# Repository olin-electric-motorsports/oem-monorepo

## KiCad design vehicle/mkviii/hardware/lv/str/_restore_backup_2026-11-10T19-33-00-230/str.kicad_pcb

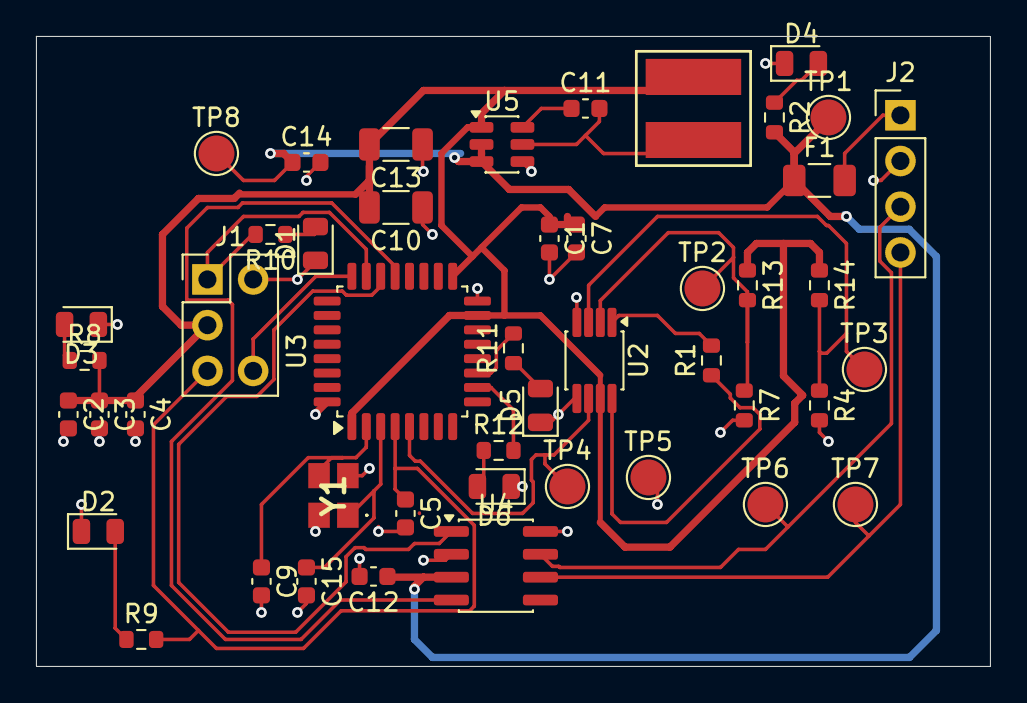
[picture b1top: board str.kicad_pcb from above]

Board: 2 copper layers, 53.0 x 35.0 mm, 47 parts (0 on the bottom side), 28 nets.

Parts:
C1: C_1uF; C_0603_1608Metric
C2, C3, C5, C11, C12: C_0.1uF; C_0603_1608Metric
C4: C_4.7uF; C_0603_1608Metric
C7: C_10uF; C_0603_1608Metric
C9, C15: C_30pF; C_0603_1608Metric
C10, C13: C_22uF; C_1206_3216Metric
C14: C_10nF; C_0603_1608Metric
D1, D2, D3, D4, D5, D6: D_Red_LED; D_0805_2012Metric
F1: F_500mA_8V; Fuse_1206_3216Metric
J1: J_Programming_Pin_Header; J_Programming_Pin_Header_Keyed
J2: Conn_01x04; PinHeader_1x04_P2.54mm_Vertical
L1: L_3.9uH; IND_BOURNS_SRR5018 (L_3.9uH_2A_55m_SMD)
R1: R_120; R_0603_1608Metric
R2, R8, R9, R10, R11, R12: R_1k; R_0603_1608Metric
R4: R_Variable; R_0603_1608Metric
R7, R13, R14: R_330; R_0603_1608Metric
TP1, TP2, TP3, TP4, TP5, TP6, TP7, TP8: TestPoint; TestPoint_Pad_D2.0mm
U2: INA333xxDGK; VSSOP-8_3x3mm_P0.65mm
U3: STM32G441KBT6; LQFP-32_7x7mm_P0.8mm
U4: MCP2561-E_SN; SOIC-8_3.9x4.9mm_P1.27mm
U5: AP63203WU-7; SOT-23-6
Y1: X_16MHz_18pF; FA238160000MBC0 (X_16MHz_18pF_SMD - FA-238_16.0000MB-C0)

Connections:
+3V3: C1.1, C2.1, C3.1, C4.1, C7.1, C10.2, C13.2, J1.3, L1.2, R8.2, R13.1, R14.1, U2.7 (V+), U3.1 (VDD), U3.15 (VDDA), U3.17 (VDD), U5.1 (FB)
+5V: C12.1, C14.1, F1.1, R2.2, TP1.1 (1_1), TP8.1 (1_1), U4.3 (VDD), U5.2 (EN), U5.3 (VIN)
/CAN_+: J2.3, TP6.1 (1_1), U4.7 (CANH)
/CAN_-: J2.4, TP7.1 (1_1), U4.6 (CANL)
/CAN_RX: U3.21 ((FDCAN1_RX/GPIO_EXTI11)PA11), U4.4 (RXD)
/CAN_TX: U3.22 ((FDCAN1_TX/GPIO_EXTI12)PA12), U4.1 (TXD)
/Debug LED: R12.2, U3.10 ((TIM2_ETR/TIM2_CH1/GPIO_EXTI5/ADC2_IN13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)
/Heartbeat LED: R11.2, U3.11 ((TIM3_CH1/TIM16_CH1/GPIO_EXTI6/ADC2_IN3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)
/NRST: C5.1, J1.4, R9.2, U3.4 ((GPIO_EXTI10)PG10-NRST)
/SWCLK: J1.5, U3.24 ((SYS_JTCK-SWCLK/GPIO_EXTI14)PA14)
/SWDIO: J1.1, R10.2, U3.23 ((SYS_JTMS-SWDIO/GPIO_EXTI13)PA13)
GND: C1.2, C2.2, C3.2, C4.2, C5.2, C7.2, C9.2, C10.1, C12.2, C13.1, C14.2, C15.2, D1.1 (K), D2.1 (K), D3.1 (K), D4.1 (K), D5.1 (K), D6.1 (K), J1.2, J2.2, R4.2, R7.2, TP5.1 (1_1), U2.4 (V-), U2.5 (Ref), U3.14 (VSSA), U3.16 (VSS), U3.32 (VSS), U4.2 (VSS), U4.8 (STBY), U5.4 (GND), Y1.2, Y1.4
unnamed: D1.2 (A), R10.1
unnamed: D2.2 (A), R9.1
unnamed: D3.2 (A), R8.1
unnamed: D4.2 (A), R2.1
unnamed: D5.2 (A), R11.1
unnamed: D6.2 (A), R12.1
unnamed: F1.2, J2.1
unnamed: R1.1, U2.8 (Rg)
unnamed: R1.2, U2.1 (Rg)
unnamed: R4.1, R14.2, TP3.1 (1_1), U2.3 (+)
unnamed: R7.1, R13.2, TP2.1 (1_1), U2.2 (-)
unnamed: TP4.1 (1_1), U2.6, U3.5 ((TIM2_ETR/TIM2_CH1/GPIO_EXTI0/ADC2_IN1/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)
unnamed: C9.1, U3.2 (PF0-OSC_IN), Y1.3
unnamed: C15.1, U3.3 (PF1-OSC_OUT), Y1.1
unnamed: C11.1, U5.6 (BST)
unnamed: C11.2, L1.1, U5.5 (SW)

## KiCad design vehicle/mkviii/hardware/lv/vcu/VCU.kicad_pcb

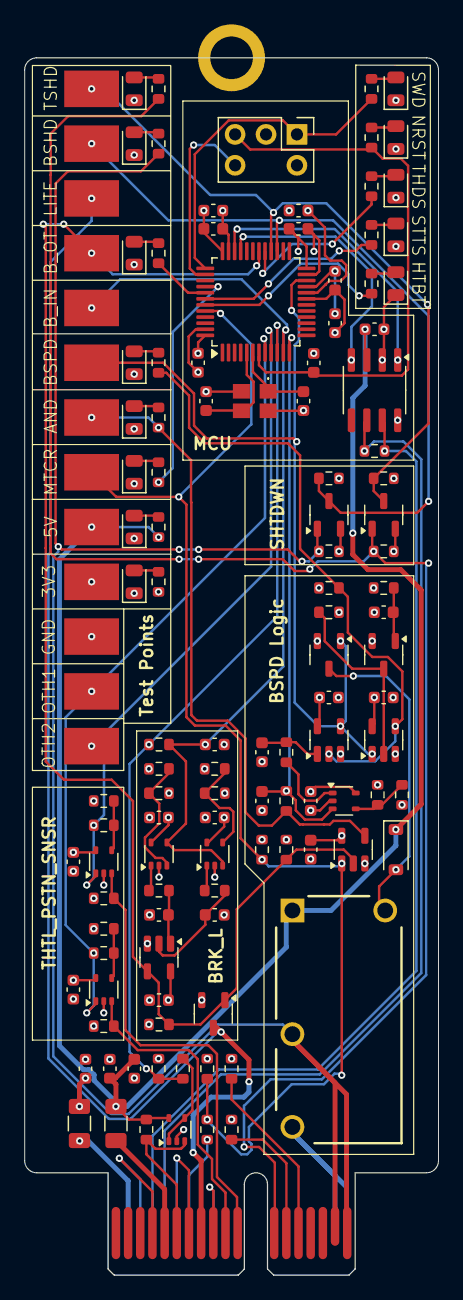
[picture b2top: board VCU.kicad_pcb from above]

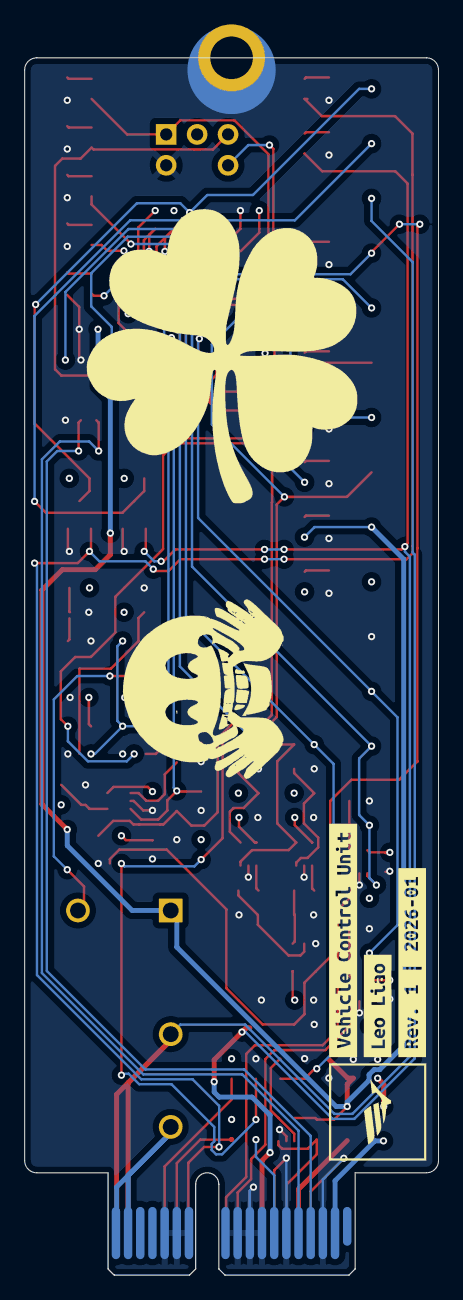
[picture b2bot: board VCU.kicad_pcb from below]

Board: 4 copper layers, 34.0 x 100.0 mm, 131 parts (3 on the bottom side), 69 nets.

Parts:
C1, C3, C5, C7, C9, C14, C15, C17, C19, C20, C21, C23, C24, C27, C28, C29: C_0.1uF; C_0603_1608Metric
C2: C_10nF; C_0603_1608Metric
C4, C18: C_1uF; C_0603_1608Metric
C6: C_4.7uF; C_0603_1608Metric
C8, C10: C_30pF; C_0603_1608Metric
C11, C26: C_0.1uF_16V; C_0603_1608Metric
C12, C13, C16: C_10uF_10V; C_0603_1608Metric
C22: C_0.22uF_50V; C_0603_1608Metric
C25: C_1uF_25V; C_0603_1608Metric
D1: MOTOR_ON; D_0805_2012Metric
D2: BRAKES; D_0805_2012Metric
D3: BSPD_TRIP; D_0805_2012Metric
D4: HEARTBEAT; D_0805_2012Metric
D5: THROTTLE_DISABLE; D_0805_2012Metric
D6: 5V; D_0805_2012Metric
D7: 3V3; D_0805_2012Metric
D8: NRST; D_0805_2012Metric
D9: SWDIO; D_0805_2012Metric
D10: D_Amber_LED; D_0805_2012Metric
D11: D_36V_500mW; D_SOD-123
D12: BSPD_TRIP_LED; D_0805_2012Metric
D13, D14: D_Blue_LED; D_0805_2012Metric
F1, F2: F_500mA_8V; Fuse_1206_3216Metric
H1: H_MountingHole
J1: J_Programming_Pin_Header; J_Programming_Pin_Header_Keyed
J2: J_PCIe_x1; J_PCIe_x1_Key
K1: K_10A_5V; G5Q1A4DC5 (K_SPST-NO_10A_5V_TH - G5Q-1A4-DC5)
Q1, Q2, Q3, Q4, Q5: SSM3K333R,LF; SOT-23-3
R1, R2, R3, R4, R5, R7, R8, R9, R12: R_200; R_0603_1608Metric
R6, R20, R27, R33: R_1k; R_0603_1608Metric
R10: R_120; R_0603_1608Metric
R11, R13, R15, R17, R22, R23, R24, R26, R28, R32, R34, R35, R36, R39, R42: R_10k; R_0603_1608Metric
R14, R16: R_5.1k; R_0603_1608Metric
R18, R19, R25, R38, R41: R_100k; R_0603_1608Metric
R21: R_71.5k; R_0603_1608Metric
R29: R_75k; R_0603_1608Metric
R30: R_576; R_0603_1608Metric
R31: R_100; R_0603_1608Metric
R37, R40: R_3k; R_0603_1608Metric
R43, R46: R_1M; R_0603_1608Metric
R44, R47: R_0; R_0603_1608Metric
R45, R48: R_2.2k; R_0603_1608Metric
TP1: 5V; TP_Hook_SMD
TP2: 3V3; TP_Hook_SMD
TP3: GND; TP_Hook_SMD
TP4, TP5, TP6, TP7, TP8, TP9, TP10, TP11, TP12, TP13: TP_SMD; TP_Hook_SMD
U1: STM32G441CBT6; LQFP-48_7x7mm_P0.5mm
U2: MCP2561-E_SN; SOIC-8_3.9x4.9mm_P1.27mm
U3, U5, U8, U9, U11, U12: MCP6001T-I/LT; SOT-353_SC-70-5
U4: SN74LVC1G08DBVR; SOT-23-5
U6, U7: SN74LVC1G02DBVR; SOT-23-5
U10: SN74LVC1G32DBVR; SOT-23-5
Y1: X_16MHz_18pF; FA238160000MBC0 (X_16MHz_18pF_SMD - FA-238_16.0000MB-C0)
kibuzzard-6983BE89: G***; kibuzzard-6983BE89
kibuzzard-6983C564: G***; kibuzzard-6983C564
kibuzzard-6983C636: G***; kibuzzard-6983C636

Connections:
+3V3: C1.1, C2.1, C3.1, C4.1, C5.1, C6.1, C7.1, C13.1, C15.2, C17.1, C20.1, C21.1, C23.1, C24.1, C27.1, C28.1, C29.1, F2.1, J1.3, R7.1, R11.1, R12.1, R18.1, R22.1, R25.1, R26.1, R30.1, R32.1, R39.1, R42.1, R43.1, R46.1, TP2.1, U1.20 (VREF+), U1.21 (VDDA), U1.24 (VDD), U1.36 (VDD), U1.48 (VDD), U4.5 (VCC), U5.5 (V+), U6.5 (VCC), U7.5 (VCC), U8.5 (V+), U9.5 (V+), U10.5 (VCC), U11.5 (V+), U12.5 (V+)
+5V: C11.1, C12.1, C14.1, D11.1 (K), F1.1, K1.1, R6.1, R13.1, TP1.1, U2.3 (VDD), U3.5 (V+)
/BSPD/BRAKELIGHT_LL: Q3.1 (G), R19.1, R36.1, TP8.1, U1.30 ((EVENTOUT/SAI1_SCK_A/SAI1_CK2/TIM4_ETR/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), U4.2, U10.4
/BSPD/BSPD_LL: Q2.1 (G), TP6.1, U1.22 ((EVENTOUT/SAI1_SCK_A/TIM1_BKIN/LPUART1_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), U6.4, U7.1
/BSPD/BSPD_RELAY_IN: J2.A17 (SHDN_IN/io_22), J2.A18 (SHDN_IN/io_24), K1.3
/BSPD/BSPD_RELAY_OUT: J2.B17 (SHDN_OUT/io_23), J2.B18 (SHDN_OUT/io_25), K1.2, Q4.1 (G), R37.1, R38.1
/BSPD/MOTOR_CURRENT_SENSE: R14.2, R15.1, R18.2, TP4.1, U1.44 ((EVENTOUT/LPTIM1_IN2/TIM3_CH4/COMP3_OUT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), U4.1
/BSPD/RC_TIMER_STATUS: C16.1, R21.2, U1.12 ((EVENTOUT/SAI1_FS_B/USART2_CK/SPI3_NSS/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), U5.3 (+)
/BrakeLight/BRAKELIGHT_CONN: J2.B8 (io_5), Q3.3 (D), TP9.1
/BrakeLight/BRAKE_PRESS_SENSE: R16.2, R17.1, R29.1, U1.10 ((EVENTOUT/UCPD1_FRSTX2/UCPD1_FRSTX1/LPU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)
/BrakeLight/BRAKE_PRESS_SENSE_FILTERED: C22.1, R29.2, TP7.1, U1.11 ((EVENTOUT/SAI1_MCLK_A/LPUART1_RX/TIM15_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), U8.4 (-), U9.3 (+)
/Microcontroller - STM32G441CBT6 (page 2)/5KW_LED: R1.1, U1.40 ((EVENTOUT/SAI1_SCK_B/TIM3_ETR/USART2_TX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)
/Microcontroller - STM32G441CBT6 (page 2)/BRAKE_LL_LED: R2.1, U1.41 ((EVENTOUT/SAI1_MCLK_B/TIM17_BKIN/USART2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)
/Microcontroller - STM32G441CBT6 (page 2)/BSPD_SHUTDOWN_SENSE: Q4.3 (D), R39.2, TP10.1, U1.27 ((EVENTOUT/LPUART1_CTS/USART3_NSS/USART3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)
/Microcontroller - STM32G441CBT6 (page 2)/BSPD_TRIP_LED: R3.1, U1.42 ((EVENTOUT/SAI1_SD_B/LPTIM1_IN1/TIM17_CH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)
/Microcontroller - STM32G441CBT6 (page 2)/CAN_+: J2.A4 (CAN+), R10.1, U2.7 (CANH)
/Microcontroller - STM32G441CBT6 (page 2)/CAN_-: J2.A5 (CAN-), R10.2, U2.6 (CANL)
/Microcontroller - STM32G441CBT6 (page 2)/CAN_RX: U1.33 ((EVENTOUT/TIM1_BKIN2/TIM1_CH4/TIM4_CH1/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), U2.4 (RXD)
/Microcontroller - STM32G441CBT6 (page 2)/CAN_TX: U1.34 ((EVENTOUT/TIM1_ETR/TIM4_CH2/FDCAN1_TX/C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), U2.1 (TXD)
/Microcontroller - STM32G441CBT6 (page 2)/HEARTBEAT_LED: R4.1, U1.43 ((EVENTOUT/SAI1_FS_B/LPTIM1_ETR/TIM8_BKI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)
/Microcontroller - STM32G441CBT6 (page 2)/NRST: C9.1, J1.4, R8.1, U1.7 ((EVENTOUT/RCC_MCO/GPIO_EXTI10)PG10-NRST)
/Microcontroller - STM32G441CBT6 (page 2)/OUTPUT_THROTTLE_1: R44.1, TP12.1, U1.8 ((EVENTOUT/TIM2_ETR/TIM8_ETR/TIM8_BKIN/C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), U11.1
/Microcontroller - STM32G441CBT6 (page 2)/OUTPUT_THROTTLE_2: R47.1, TP13.1, U1.9 ((EVENTOUT/TIM15_CH1N/USART2_DE/USART2_R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), U12.1
/Microcontroller - STM32G441CBT6 (page 2)/SS_INERTIA_OUTPUT: Q5.3 (D), R42.2, TP11.1, U1.28 ((EVENTOUT/COMP4_OUT/USART3_RTS/USART3_D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)
/Microcontroller - STM32G441CBT6 (page 2)/SWCLK: J1.5, U1.38 ((EVENTOUT/SAI1_FS_B/USART2_TX/TIM1_BKIN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)
/Microcontroller - STM32G441CBT6 (page 2)/SWDIO: J1.1, R9.1, U1.37 ((EVENTOUT/SAI1_SD_B/TIM4_CH3/USART3_NSS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)
/Microcontroller - STM32G441CBT6 (page 2)/THROTTLE_DISABLE: R5.1, U1.29 ((EVENTOUT/SPI2_MOSI/I2S2_SD/TIM1_CH3N/C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)
/PCIe x1 Connector/INPUT_THROTTLE_1: J2.B10 (io_9), R43.2, U11.3 (+)
/PCIe x1 Connector/INPUT_THROTTLE_2: J2.B11 (io_11), R46.2, U12.3 (+)
/PCIe x1 Connector/SS_INERTIA_SWITCH: J2.B12 (io_13), Q5.1 (G), R40.1, R41.1
/PCIe x1 Connector/THROTTLE_1+: J2.B13 (io_15), R11.2
/PCIe x1 Connector/THROTTLE_2+: J2.B14 (io_17), R12.2
GND: C1.2, C2.2, C3.2, C4.2, C5.2, C6.2, C7.2, C8.2, C9.2, C10.2, C11.2, C12.2, C13.2, C14.2, C15.1, C16.2, C17.2, C18.2, C19.1, C20.2, C21.2, C22.2, C23.2, C24.2, C25.2, C26.2, C27.2, C28.2, C29.2, D1.1 (K), D2.1 (K), D3.1 (K), D4.1 (K), D5.1 (K), D6.1 (K), D7.1 (K), D8.1 (K), D9.1 (K), D10.1 (K), D12.1 (K), D13.1 (K), D14.1 (K), H1.1, J1.2, J2.A3 (GND), J2.A6 (io_0), J2.A8 (io_4), J2.A9 (io_6), J2.A10 (io_8), J2.A11 (io_10), J2.A12 (io_12), J2.A13 (io_14), J2.A14 (io_16), J2.B4 (GND), J2.B7 (io_3), J2.B9 (io_7), Q1.2 (S), Q2.2 (S), Q3.2 (S), Q4.2 (S), Q5.2 (S), R15.2, R17.2, R19.2, R23.2, R28.1, R31.2, R33.2, R36.2, R38.2, R41.2, R45.2, R48.2, TP3.1, U1.19 (VSSA), U1.23 (VSS), U1.35 (VSS), U1.47 (VSS), U2.2 (VSS), U2.8 (STBY), U3.2 (V-), U4.3 (GND), U5.2 (V-), U6.3 (GND), U7.3 (GND), U8.2 (V-), U9.2 (V-), U10.3 (GND), U11.2 (V-), U12.2 (V-), Y1.2, Y1.4
unnamed: C18.1, R24.2, U6.1
unnamed: C25.1, R34.2, U10.1
unnamed: C26.1, R35.2, U10.2
unnamed: D1.2 (A), R1.2
unnamed: D2.2 (A), R2.2
unnamed: D3.2 (A), R3.2
unnamed: D4.2 (A), R4.2
unnamed: D5.2 (A), R5.2
unnamed: D6.2 (A), R6.2
unnamed: D7.2 (A), R7.2
unnamed: D8.2 (A), R8.2
unnamed: D9.2 (A), R9.2
unnamed: D10.2 (A), R20.2
unnamed: D11.2 (A), K1.5, Q2.3 (D)
unnamed: D12.2 (A), R27.2
unnamed: D13.2 (A), R37.2
unnamed: D14.2 (A), R40.2
unnamed: F2.2, J2.A2 (3.3V)
unnamed: F1.2, J2.B5 (5V)
unnamed: J2.B6 (io_1), R13.2, U3.3 (+)
unnamed: J2.A7 (io_2), R14.1
unnamed: Q1.3 (D), R25.2, U7.2
unnamed: C19.2, Q1.1 (G), R26.2
unnamed: R20.1, R21.1, TP5.1, U4.4
unnamed: R24.1, U5.1
unnamed: R27.1, R28.2, U6.2, U7.4
unnamed: R34.1, U8.1
unnamed: R35.1, U9.1
unnamed: C8.1, U1.6 ((EVENTOUT/SPI2_SCK/I2S2_CK/GPIO_EXTI1)P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), Y1.1
unnamed: C10.1, U1.5 ((EVENTOUT/TIM1_CH3N/SPI2_NSS/I2S2_WS/I2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), Y1.3
unnamed: R16.1, U3.1, U3.4 (-)
unnamed: R22.2, R23.1, U5.4 (-)
unnamed: R32.2, R33.1, U8.3 (+)
unnamed: R30.2, R31.1, U9.4 (-)
unnamed: R44.2, R45.1, U11.4 (-)
unnamed: R47.2, R48.1, U12.4 (-)

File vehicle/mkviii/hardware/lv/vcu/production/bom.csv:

Designator,Footprint,Quantity,Value,LCSC Part #
"C1, C14, C15, C17, C19, C20, C21, C23, C24, C27, C28, C29, C3, C5, C7, C9",0603,16,C_0.1uF,C0603C104Z4VACTU
"C10, C8",0603,2,C_30pF,CML0603C0G300JT50V
"C11, C26",0603,2,C_0.1uF_16V,C0603C104Z4VACTU
"C12, C13, C16",0603,3,C_10uF_10V,GRM188D71A106KA73D
"C18, C4",0603,2,C_1uF,CL10B105KA8NNNC
C2,0603,1,C_10nF,CL10B103KB8NNNC
C22,0603,1,C_0.22uF_50V,~
C25,0603,1,C_1uF_25V,CL10B105KA8NNNC
C6,0603,1,C_4.7uF,GRT188R61E475ME13D
D1,0805,1,MOTOR_ON, LTST-C171AKT 
D10,0805,1,D_Amber_LED, LTST-C171AKT 
D11,D_SOD-123,1,D_36V_500mW,BZT52C36-7-F
D12,0805,1,BSPD_TRIP_LED, LTST-C171AKT 
"D13, D14",0805,2,D_Blue_LED,LTST-C171TBKT
D2,0805,1,BRAKES, LTST-C171AKT 
D3,0805,1,BSPD_TRIP,LTST-C171KRKT
D4,0805,1,HEARTBEAT,QBLP631-IW
D5,0805,1,THROTTLE_DISABLE,QBLP631-IW
D6,0805,1,5V,QBLP631-IW
D7,0805,1,3V3,QBLP631-IW
D8,0805,1,NRST,LTST-C170KGKT
D9,0805,1,SWDIO,LTST-C170KGKT
"F1, F2",1206,2,F_500mA_8V,0ZCJ0050FF2G
J1,J_Programming_Pin_Header_Keyed,1,J_Programming_Pin_Header,
J2,J_PCIe_x1_Key,1,J_PCIe_x1,2-1761465-1
K1,G5Q1A4DC5 (K_SPST-NO_10A_5V_TH - G5Q-1A4-DC5),1,K_10A_5V,G5Q-1A4 DC5
"Q1, Q2",SOT-23-3,2,"SSM3K333R,LF","SSM3K333R,LF"
"Q3, Q4, Q5",SOT-23-3,3,"SSM3K333R,LF",
"R1, R12, R2, R3, R4, R5, R7, R8, R9",0603,9,R_200,WR06X2000FTL
R10,0603,1,R_120,RC0603FR-13120RL
"R11, R13, R15, R17, R22, R23, R24, R26, R28, R32, R34, R35, R36, R39, R42",0603,15,R_10k,RMCF0603FT10K0
"R14, R16",0603,2,R_5.1k,CR0603AFX-5101EAS
"R18, R19, R25, R38, R41",0603,5,R_100k,RMCF0603FT100K
"R20, R27, R33, R6",0603,4,R_1k,RMCF0603FT1K00 (or ERJ-3GEYJ102V)
R21,0603,1,R_71.5k,RMCF0603FT71K5
R29,0603,1,R_75k,RMCF0603FT75K0
R30,0603,1,R_576,RMCF0603FT576R
R31,0603,1,R_100,RMCF0603FT100R
"R37, R40",0603,2,R_3k,RC0603FR-103KL
"R43, R46",0603,2,R_1M,WR06X1004FTL
"R44, R47",0603,2,R_0,RMCF0603ZT0R00
"R45, R48",0603,2,R_2.2k,WR06X222 JTL
TP1,TP_Hook_SMD,1,5V,5019
"TP10, TP11, TP12, TP13, TP4, TP5, TP6, TP7, TP8, TP9",TP_Hook_SMD,10,TP_SMD,5019
TP2,TP_Hook_SMD,1,3V3,5019
TP3,TP_Hook_SMD,1,GND,5019
U1,LQFP-48_7x7mm_P0.5mm,1,STM32G441CBT6,STM32G441CBT6
U10,SOT-23-5,1,SN74LVC1G32DBVR,SN74LVC1G32DBVR
"U11, U12, U3, U5, U8, U9",SOT-353_SC-70-5,6,MCP6001T-I/LT,MCP6001T-I/LT
U2,SOIC-8_3.9x4.9mm_P1.27mm,1,MCP2561-E_SN,MCP2561-E/SN
U4,SOT-23-5,1,SN74LVC1G08DBVR,SN74LVC1G08DBVR
"U6, U7",SOT-23-5,2,SN74LVC1G02DBVR,SN74LVC1G02DBVR
Y1,FA238160000MBC0 (X_16MHz_18pF_SMD - FA-238_16.0000MB-C0),1,X_16MHz_18pF,FA-238 16.0000MB-C0

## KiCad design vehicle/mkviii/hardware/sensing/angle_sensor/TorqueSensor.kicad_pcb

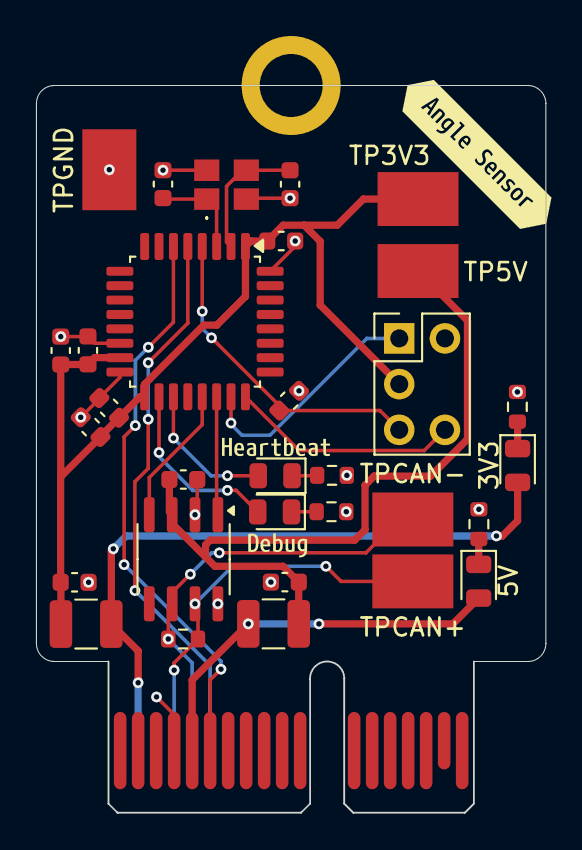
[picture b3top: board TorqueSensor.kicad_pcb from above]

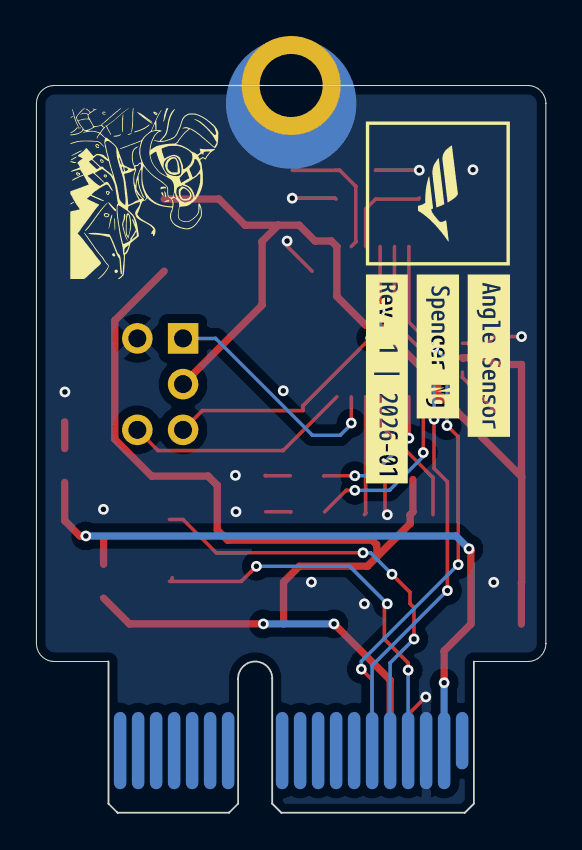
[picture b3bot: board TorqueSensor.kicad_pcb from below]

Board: 2 copper layers, 28.3 x 40.4 mm, 39 parts (3 on the bottom side), 22 nets.

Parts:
3V3, 5V: LED_WHITE; D_0805_2012Metric
C1: C_0.1uF_16V; C_0603_1608Metric
C2, C9: C_30pF_50V; C_0603_1608Metric
C3: C_4.7uF_25V; C_0603_1608Metric
C4, C5, C8: C_0.1uF_50V; C_0603_1608Metric
C6: C_1uF_50V; C_0603_1608Metric
C7: C_10nF_50V; C_0603_1608Metric
C10, C11: C_10uF_10V; C_0603_1608Metric
D1: LED_AMBER; D_0805_2012Metric
D2: LED_WHITE; D_0805_2012Metric
F1, F2: F_500mA_16V; Fuse_1210_3225Metric
H1: H_MountingHole
J1: J_PCIe_x1; J_PCIe_x1_Key
J2: J_Programming_Pin_Header; J_Programming_Pin_Header_Keyed
R1, R3, R4, R5: R_1k; R_0603_1608Metric
R2: R_120; R_0603_1608Metric
TP3V3, TP5V: TP_SMD; TP_Hook_SMD
TPCAN+: TP_SMD; TP_Hook_SMD
TPCAN-: TP_SMD; TP_Hook_SMD
TPGND: TP_SMD; TP_Hook_SMD
U2: STM32G441KBT6; LQFP-32_7x7mm_P0.8mm
U3: MCP2561-E_SN; SOIC-8_3.9x4.9mm_P1.27mm
Y1: X_16MHz_18pF; FA238160000MBC0 (X_16MHz_18pF_SMD - FA-238_16.0000MB-C0)
kibuzzard-697FF3E2: G***; kibuzzard-697FF3E2
kibuzzard-697FF3F7: G***; kibuzzard-697FF3F7
kibuzzard-697FF4A8: G***; kibuzzard-697FF4A8
kibuzzard-697FF7D3: G***; kibuzzard-697FF7D3
kibuzzard-697FF82D: G***; kibuzzard-697FF82D
kibuzzard-697FF937: G***; kibuzzard-697FF937

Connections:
+3V3: C3.1, C4.1, C5.1, C6.1, C7.1, C10.1, F1.1, J2.3, TP3V3.1, U2.1 (VDD), U2.15 (VDDA), U2.17 (VDD)
+5V: C1.1, C11.1, F2.1, TP5V.1, U3.3 (VDD)
/CAN_+: J1.A4 (CAN+), R2.2, TPCAN+.1, U3.7 (CANH)
/CAN_-: J1.A5 (CAN-), R2.1, TPCAN-.1, U3.6 (CANL)
/CAN_RX: U2.21 ((FDCAN1_RX/GPIO_EXTI11)PA11), U3.4 (RXD)
/CAN_TX: U2.22 ((FDCAN1_TX/GPIO_EXTI12)PA12), U3.1 (TXD)
/DEBUG_LED: D1.2 (A), U2.18 ((TIM4_ETR/USART1_CK/GPIO_EXTI8)PA8)
/HEARTBEAT_LED: D2.2 (A), U2.19 ((TIM2_CH3/TIM15_BKIN/USART1_TX/GPIO_EXT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)
/NRST: C8.1, J2.4, U2.4 ((GPIO_EXTI10)PG10-NRST)
/PWM_Input: J1.A6 (io_0), U2.5 ((TIM2_ETR/TIM2_CH1/GPIO_EXTI0/ADC2_IN1/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)
/SWCLK: J2.5, U2.24 ((SYS_JTCK-SWCLK/GPIO_EXTI14)PA14)
/SWDIO: J2.1, U2.23 ((SYS_JTMS-SWDIO/GPIO_EXTI13)PA13)
/Status_Signal_Input: J1.B6 (io_1), U2.6 ((TIM15_CH1N/TIM2_CH2/GPIO_EXTI1/ADC2_IN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)
GND: C1.2, C2.2, C3.2, C4.2, C5.2, C6.2, C7.2, C8.2, C9.2, C10.2, C11.2, H1.1, J1.A3 (GND), J1.B4 (GND), J2.2, R1.2, R3.2, R4.2, R5.2, TPGND.1, U2.14 (VSSA), U2.16 (VSS), U2.32 (VSS), U3.2 (VSS), U3.8 (STBY), Y1.2, Y1.4
unnamed: D1.1 (K), R3.1
unnamed: D2.1 (K), R4.1
unnamed: 3V3.2 (A), F1.2, J1.A2 (3.3V)
unnamed: 3V3.1 (K), R1.1
unnamed: 5V.2 (A), F2.2, J1.B5 (5V)
unnamed: 5V.1 (K), R5.1
unnamed: C9.1, U2.2 (PF0-OSC_IN), Y1.3
unnamed: C2.1, U2.3 (PF1-OSC_OUT), Y1.1

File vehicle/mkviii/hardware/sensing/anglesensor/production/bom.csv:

Designator,Footprint,Quantity,Value,LCSC Part #
"3V3, 5V, D2",0805,3,LED_WHITE,QBLP631-IW
C1,0603,1,C_0.1uF_16V,C0603C104Z4VACTU
"C10, C11",0603,2,C_10uF_10V,GRM188D71A106KA73D
"C2, C9",0603,2,C_30pF_50V,CML0603C0G300JT50V
C3,0603,1,C_4.7uF_25V,GRT188R61E475ME13D
"C4, C5, C8",0603,3,C_0.1uF_50V,CL10B104KB8NNWC
C6,0603,1,C_1uF_50V,UMK107BJ105KA-T
C7,0603,1,C_10nF_50V,CL10B103KB8NNNC
D1,0805,1,LED_AMBER,QBLP631-IW
"F1, F2",1210,2,F_500mA_16V,0ZCH0050FF2G
J1,J_PCIe_x1_Key,1,J_PCIe_x1,2-1761465-1
J2,J_Programming_Pin_Header_Keyed,1,J_Programming_Pin_Header,
"R1, R3, R4, R5",0603,4,R_1k,RMCF0603FT1K00 (or ERJ-3GEYJ102V)
R2,0603,1,R_120,RC0603FR-13120RL
"TP3V3, TP5V, TPCAN+, TPCAN-, TPGND",TP_Hook_SMD,5,TP_SMD,5019
U2,LQFP-32_7x7mm_P0.8mm,1,STM32G441KBT6,
U3,SOIC-8_3.9x4.9mm_P1.27mm,1,MCP2561-E_SN,MCP2561-E/SN
Y1,FA238160000MBC0 (X_16MHz_18pF_SMD - FA-238_16.0000MB-C0),1,X_16MHz_18pF,FA-238 16.0000MB-C0

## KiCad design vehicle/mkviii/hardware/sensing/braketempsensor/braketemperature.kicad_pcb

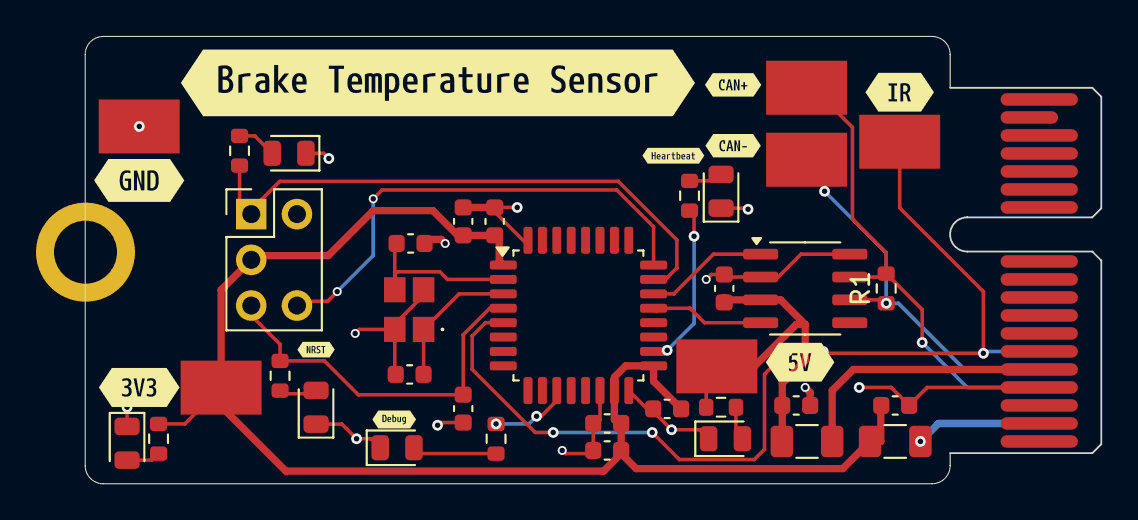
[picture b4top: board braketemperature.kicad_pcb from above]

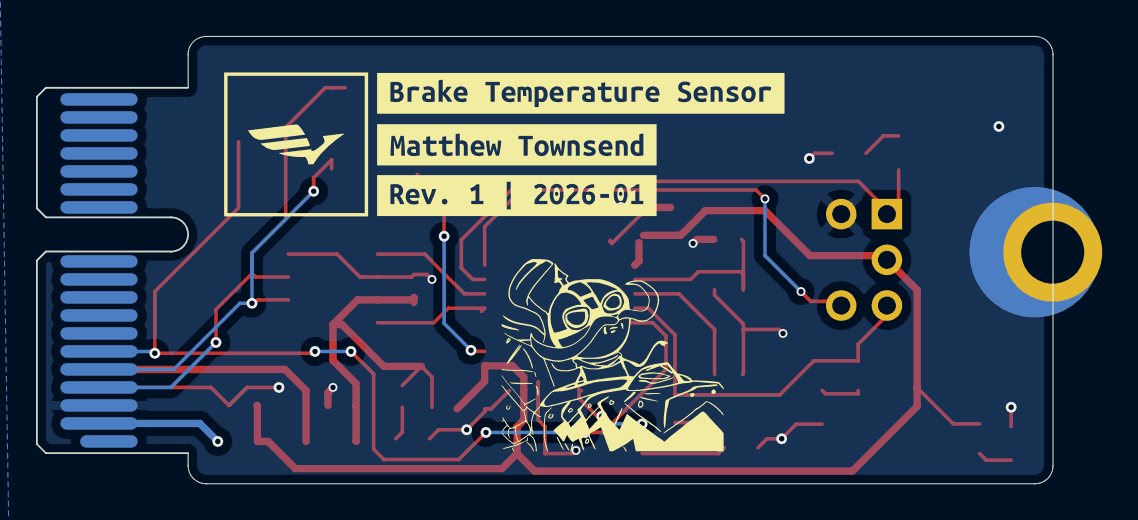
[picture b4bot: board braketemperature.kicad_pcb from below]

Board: 2 copper layers, 56.4 x 24.9 mm, 51 parts (3 on the bottom side), 23 nets.

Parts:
C1, C2, C4, C7: C_0.1uF; C_0603_1608Metric
C3: C_10nF; C_0603_1608Metric
C5: C_1uF; C_0603_1608Metric
C6: C_4.7uF; C_0603_1608Metric
C8, C9: C_30pF; C_0603_1608Metric
C10, C11: C_10uF_10V; C_0603_1608Metric
D1, D2, D3, D4, D5, D6: D_Red_LED; D_0805_2012Metric
F1, F2: F_500mA_8V; Fuse_1206_3216Metric
H1: H_MountingHole
J1: J_PCIe_x1; J_PCIe_x1_Key
J2: J_Programming_Pin_Header; J_Programming_Pin_Header_Keyed
R1: R_120; R_0603_1608Metric
R2, R3, R4, R5, R6, R7: R_1k; R_0603_1608Metric
TP1, TP2, TP3, TP4, TP5, TP6: TP_SMD; TP_Hook_SMD
U1: MCP2561-E_SN; SOIC-8_3.9x4.9mm_P1.27mm
U2: STM32G441KBT6; LQFP-32_7x7mm_P0.8mm
Y1: X_16MHz_18pF; FA238160000MBC0 (X_16MHz_18pF_SMD - FA-238_16.0000MB-C0)
kibuzzard-697E6E94: G***; kibuzzard-697E6E94
kibuzzard-697E6EEF: G***; kibuzzard-697E6EEF
kibuzzard-697E6F70: G***; kibuzzard-697E6F70
kibuzzard-697E6FE4: G***; kibuzzard-697E6FE4
kibuzzard-697F80A9: G***; kibuzzard-697F80A9
kibuzzard-697F80BA: G***; kibuzzard-697F80BA
kibuzzard-697F802E: G***; kibuzzard-697F802E
kibuzzard-69815F9D: G***; kibuzzard-69815F9D
kibuzzard-69815FEC: G***; kibuzzard-69815FEC
kibuzzard-69815FF8: G***; kibuzzard-69815FF8
kibuzzard-69816079: G***; kibuzzard-69816079
kibuzzard-69816083: G***; kibuzzard-69816083
kibuzzard-69816091: G***; kibuzzard-69816091

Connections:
+3V3: C2.1, C3.1, C4.1, C5.1, C6.1, C11.1, F2.1, J2.3, R3.1, TP3.1, U2.1 (VDD), U2.15 (VDDA), U2.17 (VDD)
+5V: C1.1, C10.1, F1.1, R2.1, TP2.1, U1.3 (VDD)
/CAN_RX: U1.4 (RXD), U2.21 ((FDCAN1_RX/GPIO_EXTI11)PA11)
/CAN_TX: U1.1 (TXD), U2.22 ((FDCAN1_TX/GPIO_EXTI12)PA12)
/Debug LED: R5.1, U2.11 ((TIM3_CH1/TIM16_CH1/GPIO_EXTI6/ADC2_IN3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)
/Heartbeat LED: R4.1, U2.18 ((TIM4_ETR/USART1_CK/GPIO_EXTI8)PA8)
/IR Output - PA0: J1.A6 (io_0), TP1.1, U2.5 ((TIM2_ETR/TIM2_CH1/GPIO_EXTI0/ADC2_IN1/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)
/NRST: C7.1, J2.4, R6.1, U2.4 ((GPIO_EXTI10)PG10-NRST)
/SWCLK: J2.5, U2.24 ((SYS_JTCK-SWCLK/GPIO_EXTI14)PA14)
/SWDIO: J2.1, R7.1, U2.23 ((SYS_JTMS-SWDIO/GPIO_EXTI13)PA13)
GND: C1.2, C2.2, C3.2, C4.2, C5.2, C6.2, C7.2, C8.2, C9.2, C10.2, C11.2, D1.1 (K), D2.1 (K), D3.1 (K), D4.1 (K), D5.1 (K), D6.1 (K), H1.1, J1.A3 (GND), J1.B4 (GND), J2.2, TP6.1, U1.2 (VSS), U1.8 (STBY), U2.14 (VSSA), U2.16 (VSS), U2.32 (VSS), Y1.2, Y1.4
unnamed: D1.2 (A), R2.2
unnamed: D2.2 (A), R3.2
unnamed: D3.2 (A), R4.2
unnamed: D4.2 (A), R5.2
unnamed: D5.2 (A), R6.2
unnamed: D6.2 (A), R7.2
unnamed: F2.2, J1.A2 (3.3V)
unnamed: F1.2, J1.B5 (5V)
unnamed: J1.A4 (CAN+), R1.2, TP4.1, U1.7 (CANH)
unnamed: J1.A5 (CAN-), R1.1, TP5.1, U1.6 (CANL)
unnamed: C9.1, U2.2 (PF0-OSC_IN), Y1.3
unnamed: C8.1, U2.3 (PF1-OSC_OUT), Y1.1

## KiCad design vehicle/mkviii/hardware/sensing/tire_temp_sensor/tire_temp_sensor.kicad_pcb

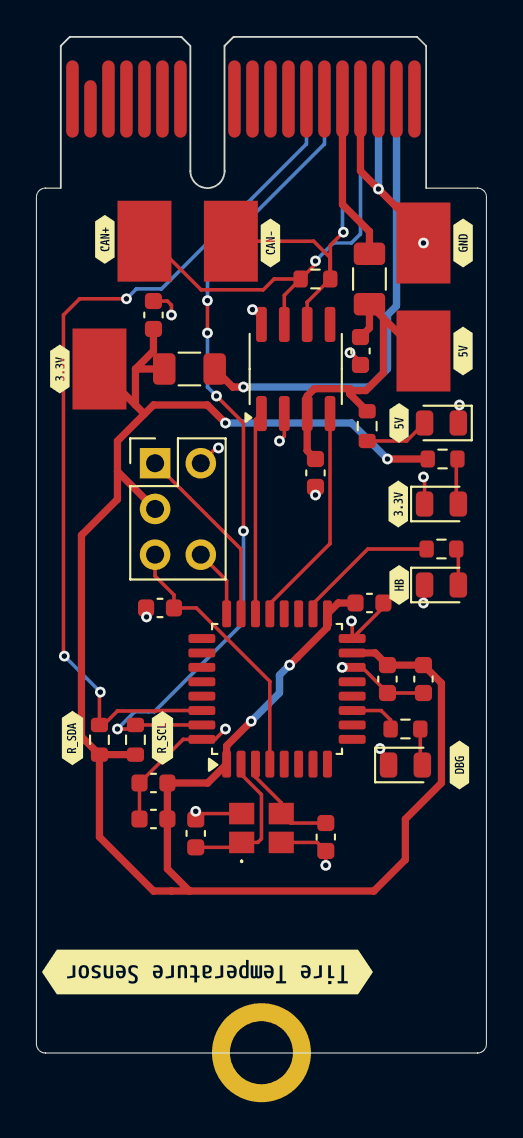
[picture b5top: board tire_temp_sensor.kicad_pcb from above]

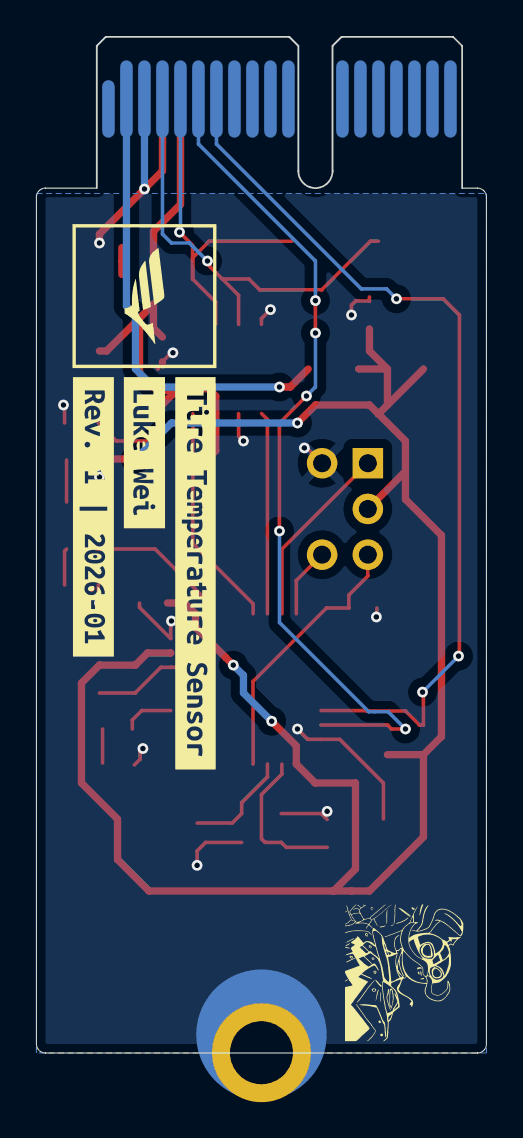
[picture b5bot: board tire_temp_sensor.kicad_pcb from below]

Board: 2 copper layers, 25.0 x 56.5 mm, 50 parts (3 on the bottom side), 22 nets.

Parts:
C1: C_4.7uF_25V; C_0603_1608Metric
C2, C5, C7, C11: C_0.1uF_16V; C_0603_1608Metric
C3, C6: C_30pF_50V; C_0603_1608Metric
C4: C_1uF_50V; C_0603_1608Metric
C8, C9: C_10uF_10V; C_0603_1608Metric
C10: C_10nF_50V; C_0603_1608Metric
D1, D2, D3, D4: D_Blue_LED; D_0805_2012Metric
F1, F3: F_500mA_8V; Fuse_1206_3216Metric
H2: H_MountingHole
J2: J_PCIe_x1; J_PCIe_x1_Key
J3: J_Programming_Pin_Header; J_Programming_Pin_Header_Keyed
R1, R2: R_2.2k_0.1W; R_0603_1608Metric
R3: R_120; R_0603_1608Metric
R4, R5, R6, R7: R_1k; R_0603_1608Metric
TP1, TP2, TP3, TP4, TP5: TP_SMD; TP_Hook_SMD
U1: STM32G441KBT6; LQFP-32_7x7mm_P0.8mm
U2: MCP2561-E_SN; SOIC-8_3.9x4.9mm_P1.27mm
Y1: X_16MHz_18pF; FA238160000MBC0 (X_16MHz_18pF_SMD - FA-238_16.0000MB-C0)
kibuzzard-697E5AB9: G***; kibuzzard-697E5AB9
kibuzzard-697E5B7C: G***; kibuzzard-697E5B7C
kibuzzard-697E5B13: G***; kibuzzard-697E5B13
kibuzzard-697E5B64: G***; kibuzzard-697E5B64
kibuzzard-697E5B74: G***; kibuzzard-697E5B74
kibuzzard-697E5BB9: G***; kibuzzard-697E5BB9
kibuzzard-697E5C85: G***; kibuzzard-697E5C85
kibuzzard-697E5DCC: G***; kibuzzard-697E5DCC
kibuzzard-697E5E44: G***; kibuzzard-697E5E44
kibuzzard-697E730B: G***; kibuzzard-697E730B
kibuzzard-6980A3A7: G***; kibuzzard-6980A3A7
kibuzzard-6980A425: G***; kibuzzard-6980A425
kibuzzard-6980A498: G***; kibuzzard-6980A498
kibuzzard-698147C7: G***; kibuzzard-698147C7
kibuzzard-69814769: G***; kibuzzard-69814769

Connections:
+3.3V: C1.1, C4.1, C5.1, C8.1, C10.1, C11.1, F3.1, J3.3, R1.1, R2.1, R6.1, TP1.1, U1.1 (VDD), U1.15 (VDDA), U1.17 (VDD)
+5V: C7.1, C9.1, F1.1, R7.1, TP3.1, U2.3 (VDD)
/CAN_+: J2.A4 (CAN+), R3.1, TP5.1, U2.7 (CANH)
/CAN_-: J2.A5 (CAN-), R3.2, TP4.1, U2.6 (CANL)
/CAN_RX: U1.21 ((FDCAN1_RX/GPIO_EXTI11)PA11), U2.4 (RXD)
/CAN_TX: U1.22 ((FDCAN1_TX/GPIO_EXTI12)PA12), U2.1 (TXD)
/Debug LED: R5.1, U1.11 ((TIM3_CH1/TIM16_CH1/GPIO_EXTI6/ADC2_IN3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)
/Heartbeat LED: R4.1, U1.18 ((TIM4_ETR/USART1_CK/GPIO_EXTI8)PA8)
/I2C1_SCL: J2.A6 (io_0), R1.2, U1.31 ((TIM4_CH3/TIM16_CH1/GPIO_EXTI8)PB8-BOOT0)
/I2C1_SDA: J2.A7 (io_2), R2.2, U1.30 ((TIM3_CH4/TIM4_CH2/TIM17_CH1N/GPIO_EXTI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)
/NRST: C2.1, J3.4, U1.4 ((GPIO_EXTI10)PG10-NRST)
/SWCLK: J3.5, U1.24 ((SYS_JTCK-SWCLK/GPIO_EXTI14)PA14)
/SWDIO: J3.1, U1.23 ((SYS_JTMS-SWDIO/GPIO_EXTI13)PA13)
GND: C1.2, C2.2, C3.2, C4.2, C5.2, C6.2, C7.2, C8.2, C9.2, C10.2, C11.2, D1.1 (K), D2.1 (K), D3.1 (K), D4.1 (K), H2.1, J2.A3 (GND), J2.B4 (GND), J3.2, TP2.1, U1.14 (VSSA), U1.16 (VSS), U1.32 (VSS), U2.2 (VSS), U2.8 (STBY), Y1.2, Y1.4
unnamed: D1.2 (A), R5.2
unnamed: D2.2 (A), R4.2
unnamed: D3.2 (A), R6.2
unnamed: D4.2 (A), R7.2
unnamed: F3.2, J2.A2 (3.3V)
unnamed: F1.2, J2.B5 (5V)
unnamed: C6.1, U1.2 (PF0-OSC_IN), Y1.1
unnamed: C3.1, U1.3 (PF1-OSC_OUT), Y1.3

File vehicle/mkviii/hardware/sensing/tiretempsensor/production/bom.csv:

Designator,Footprint,Quantity,Value,LCSC Part #
C1,0603,1,C_4.7uF_25V,GRT188R61E475ME13D
C10,0603,1,C_10nF_50V,CL10B103KB8NNNC
"C11, C2, C5, C7",0603,4,C_0.1uF_16V,C0603C104Z4VACTU
"C3, C6",0603,2,C_30pF_50V,CML0603C0G300JT50V
C4,0603,1,C_1uF_50V,UMK107BJ105KA-T
"C8, C9",0603,2,C_10uF_10V,GRM188D71A106KA73D
"D1, D2, D3, D4",0805,4,D_Blue_LED,LTST-C171TBKT
"F1, F3",1206,2,F_500mA_8V,0ZCJ0050FF2G
J2,J_PCIe_x1_Key,1,J_PCIe_x1,2-1761465-1
J3,J_Programming_Pin_Header_Keyed,1,J_Programming_Pin_Header,
"R1, R2",0603,2,R_2.2k_0.1W,WR06X222 JTL
R3,0603,1,R_120,RC0603FR-13120RL
"R4, R5, R6, R7",0603,4,R_1k,RMCF0603FT1K00 (or ERJ-3GEYJ102V)
"TP1, TP2, TP3, TP4, TP5",TP_Hook_SMD,5,TP_SMD,5019
U1,LQFP-32_7x7mm_P0.8mm,1,STM32G441KBT6,
U2,SOIC-8_3.9x4.9mm_P1.27mm,1,MCP2561-E_SN,MCP2561-E/SN
Y1,FA238160000MBC0 (X_16MHz_18pF_SMD - FA-238_16.0000MB-C0),1,X_16MHz_18pF,FA-238 16.0000MB-C0
